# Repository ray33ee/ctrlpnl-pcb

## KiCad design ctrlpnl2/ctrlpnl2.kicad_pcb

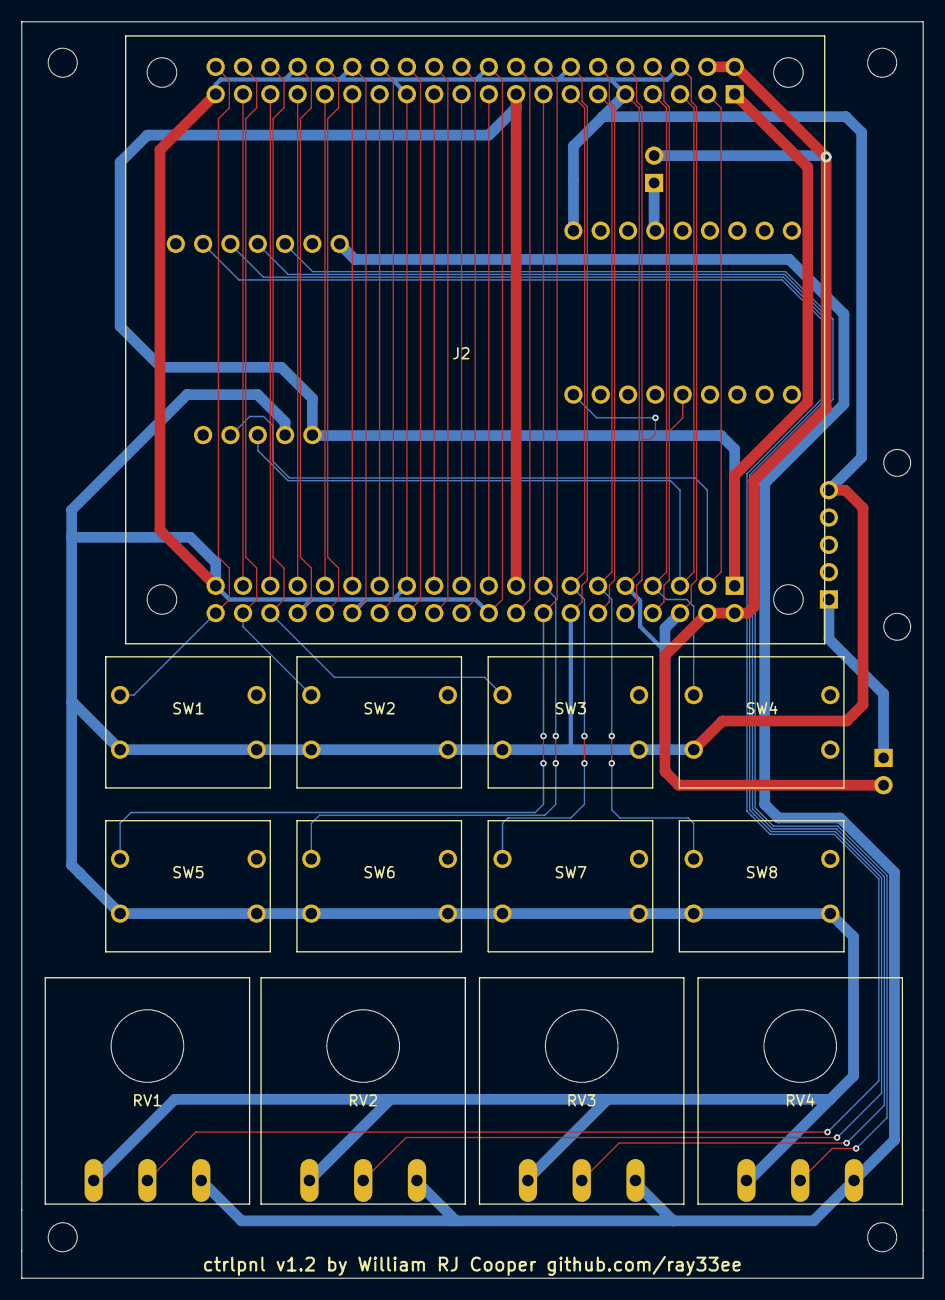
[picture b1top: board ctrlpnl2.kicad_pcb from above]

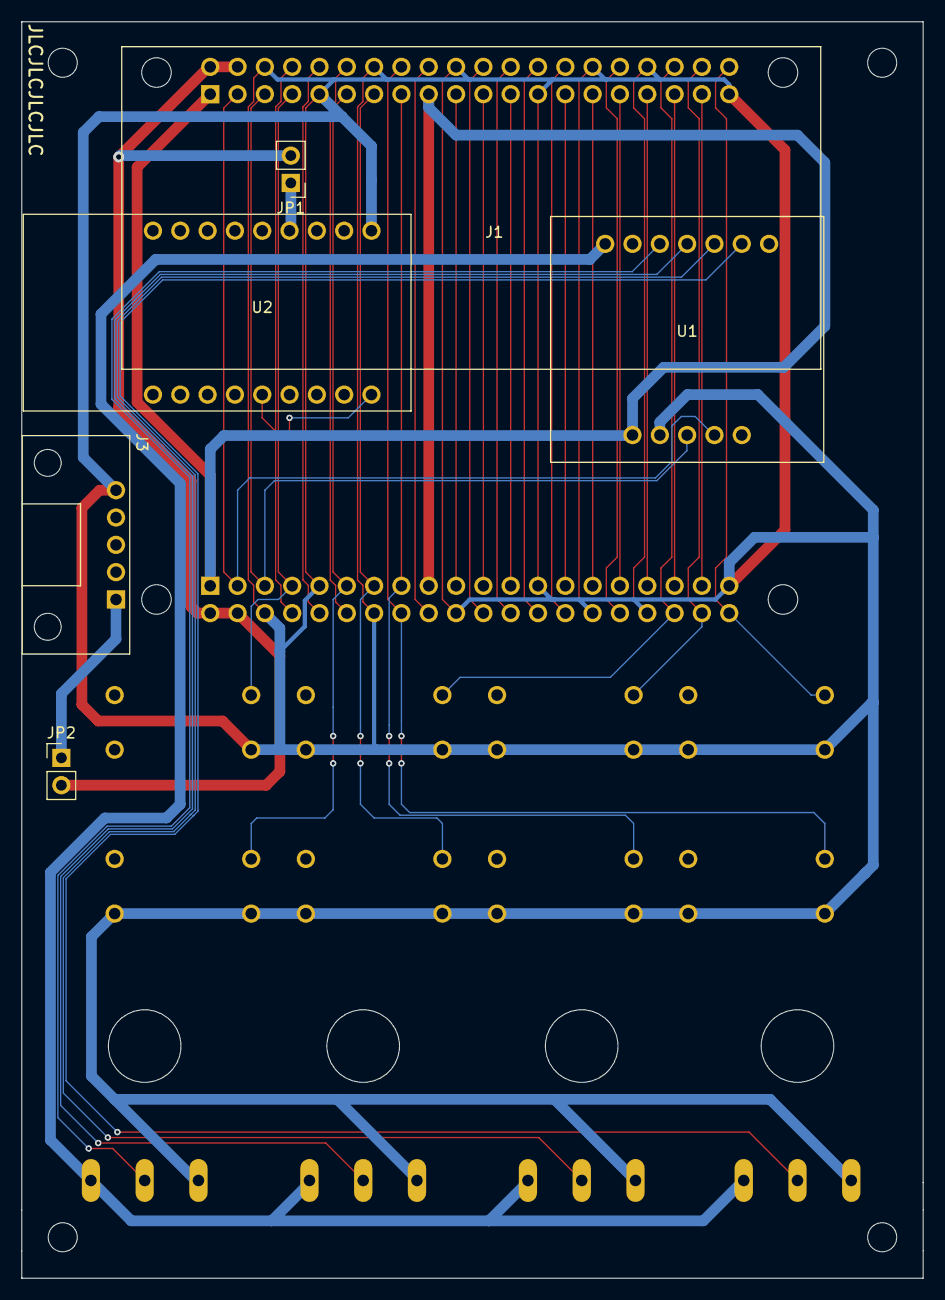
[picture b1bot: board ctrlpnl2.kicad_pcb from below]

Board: 2 copper layers, 83.8 x 116.8 mm, 19 parts (6 on the bottom side), 38 nets.

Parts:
J1: Raspberry_Pi_Header; Pi Zero
J2: Adafruit_TouchScreen_Header; Adafruit 2.4'' 320x240 Touchscreen
J3: Micro_USB_Breakout; Adafruit_Micro_USB_Breakout
JP1, JP2: Jumper_2_Open; PinHeader_1x02_P2.54mm_Vertical
RV1, RV2, RV3, RV4: R_POT; WH148-1A-2
SW1, SW2, SW3, SW4, SW5, SW6, SW7, SW8: SW_MEC_5E; Switch
U1: Adafruit_PCF8591_Breakout; Adafruit_PCF8591
U2: USB_To_TTL; USBtoTTL

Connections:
+3V3: J1.1, J2.1, U1.8
+5V: J1.2, J2.2, JP1.2, JP2.2
/POT_A0: RV1.2, U1.6
/POT_A1: RV2.2, U1.5
/POT_A2: RV3.2, U1.4
/POT_A3: RV4.2, U1.3
/PWR_USB_5V: J3.1, JP2.1
/TTL_USB_5V: JP1.1, U2.13
/Vref: RV1.3, RV2.3, RV3.3, RV4.3, U1.1
GND: J1.6, J2.6, J3.5, RV1.1, RV2.1, RV3.1, RV4.1, SW1.2, SW1.3, SW2.2, SW2.3, SW3.2, SW3.3, SW4.2, SW5.2, SW5.3, SW6.2, SW6.3, SW7.2, SW7.3, SW8.2, SW8.3, U1.9, U2.10
PI_J_7: J1.7, J2.7, SW4.1
PI_J_11: J1.11, J2.11, SW8.1
PI_J_12: J1.12, J2.12
PI_J_13: J1.13, J2.13, SW7.1
PI_J_15: J1.15, J2.15, SW6.1
PI_J_16: J1.16, J2.16, SW5.1
PI_J_18: J1.18, J2.18
PI_J_19: J1.19, J2.19
PI_J_21: J1.21, J2.21
PI_J_22: J1.22, J2.22
PI_J_23: J1.23, J2.23
PI_J_24: J1.24, J2.24
PI_J_26: J1.26, J2.26
PI_J_27: J1.27, J2.27
PI_J_28: J1.28, J2.28
PI_J_29: J1.29, J2.29
PI_J_31: J1.31, J2.31
PI_J_32: J1.32, J2.32
PI_J_33: J1.33, J2.33
PI_J_35: J1.35, J2.35
PI_J_36: J1.36, J2.36, SW3.1
PI_J_37: J1.37, J2.37
PI_J_38: J1.38, J2.38, SW2.1
PI_J_40: J1.40, J2.40, SW1.1
PI_RX: J1.10, J2.10, U2.1
PI_SCL1: J1.5, J2.5, U1.10
PI_SDA1: J1.3, J2.3, U1.11
PI_TX: J1.8, J2.8, U2.5

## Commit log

2021-08-05 Version 1.2 - Initial commit
